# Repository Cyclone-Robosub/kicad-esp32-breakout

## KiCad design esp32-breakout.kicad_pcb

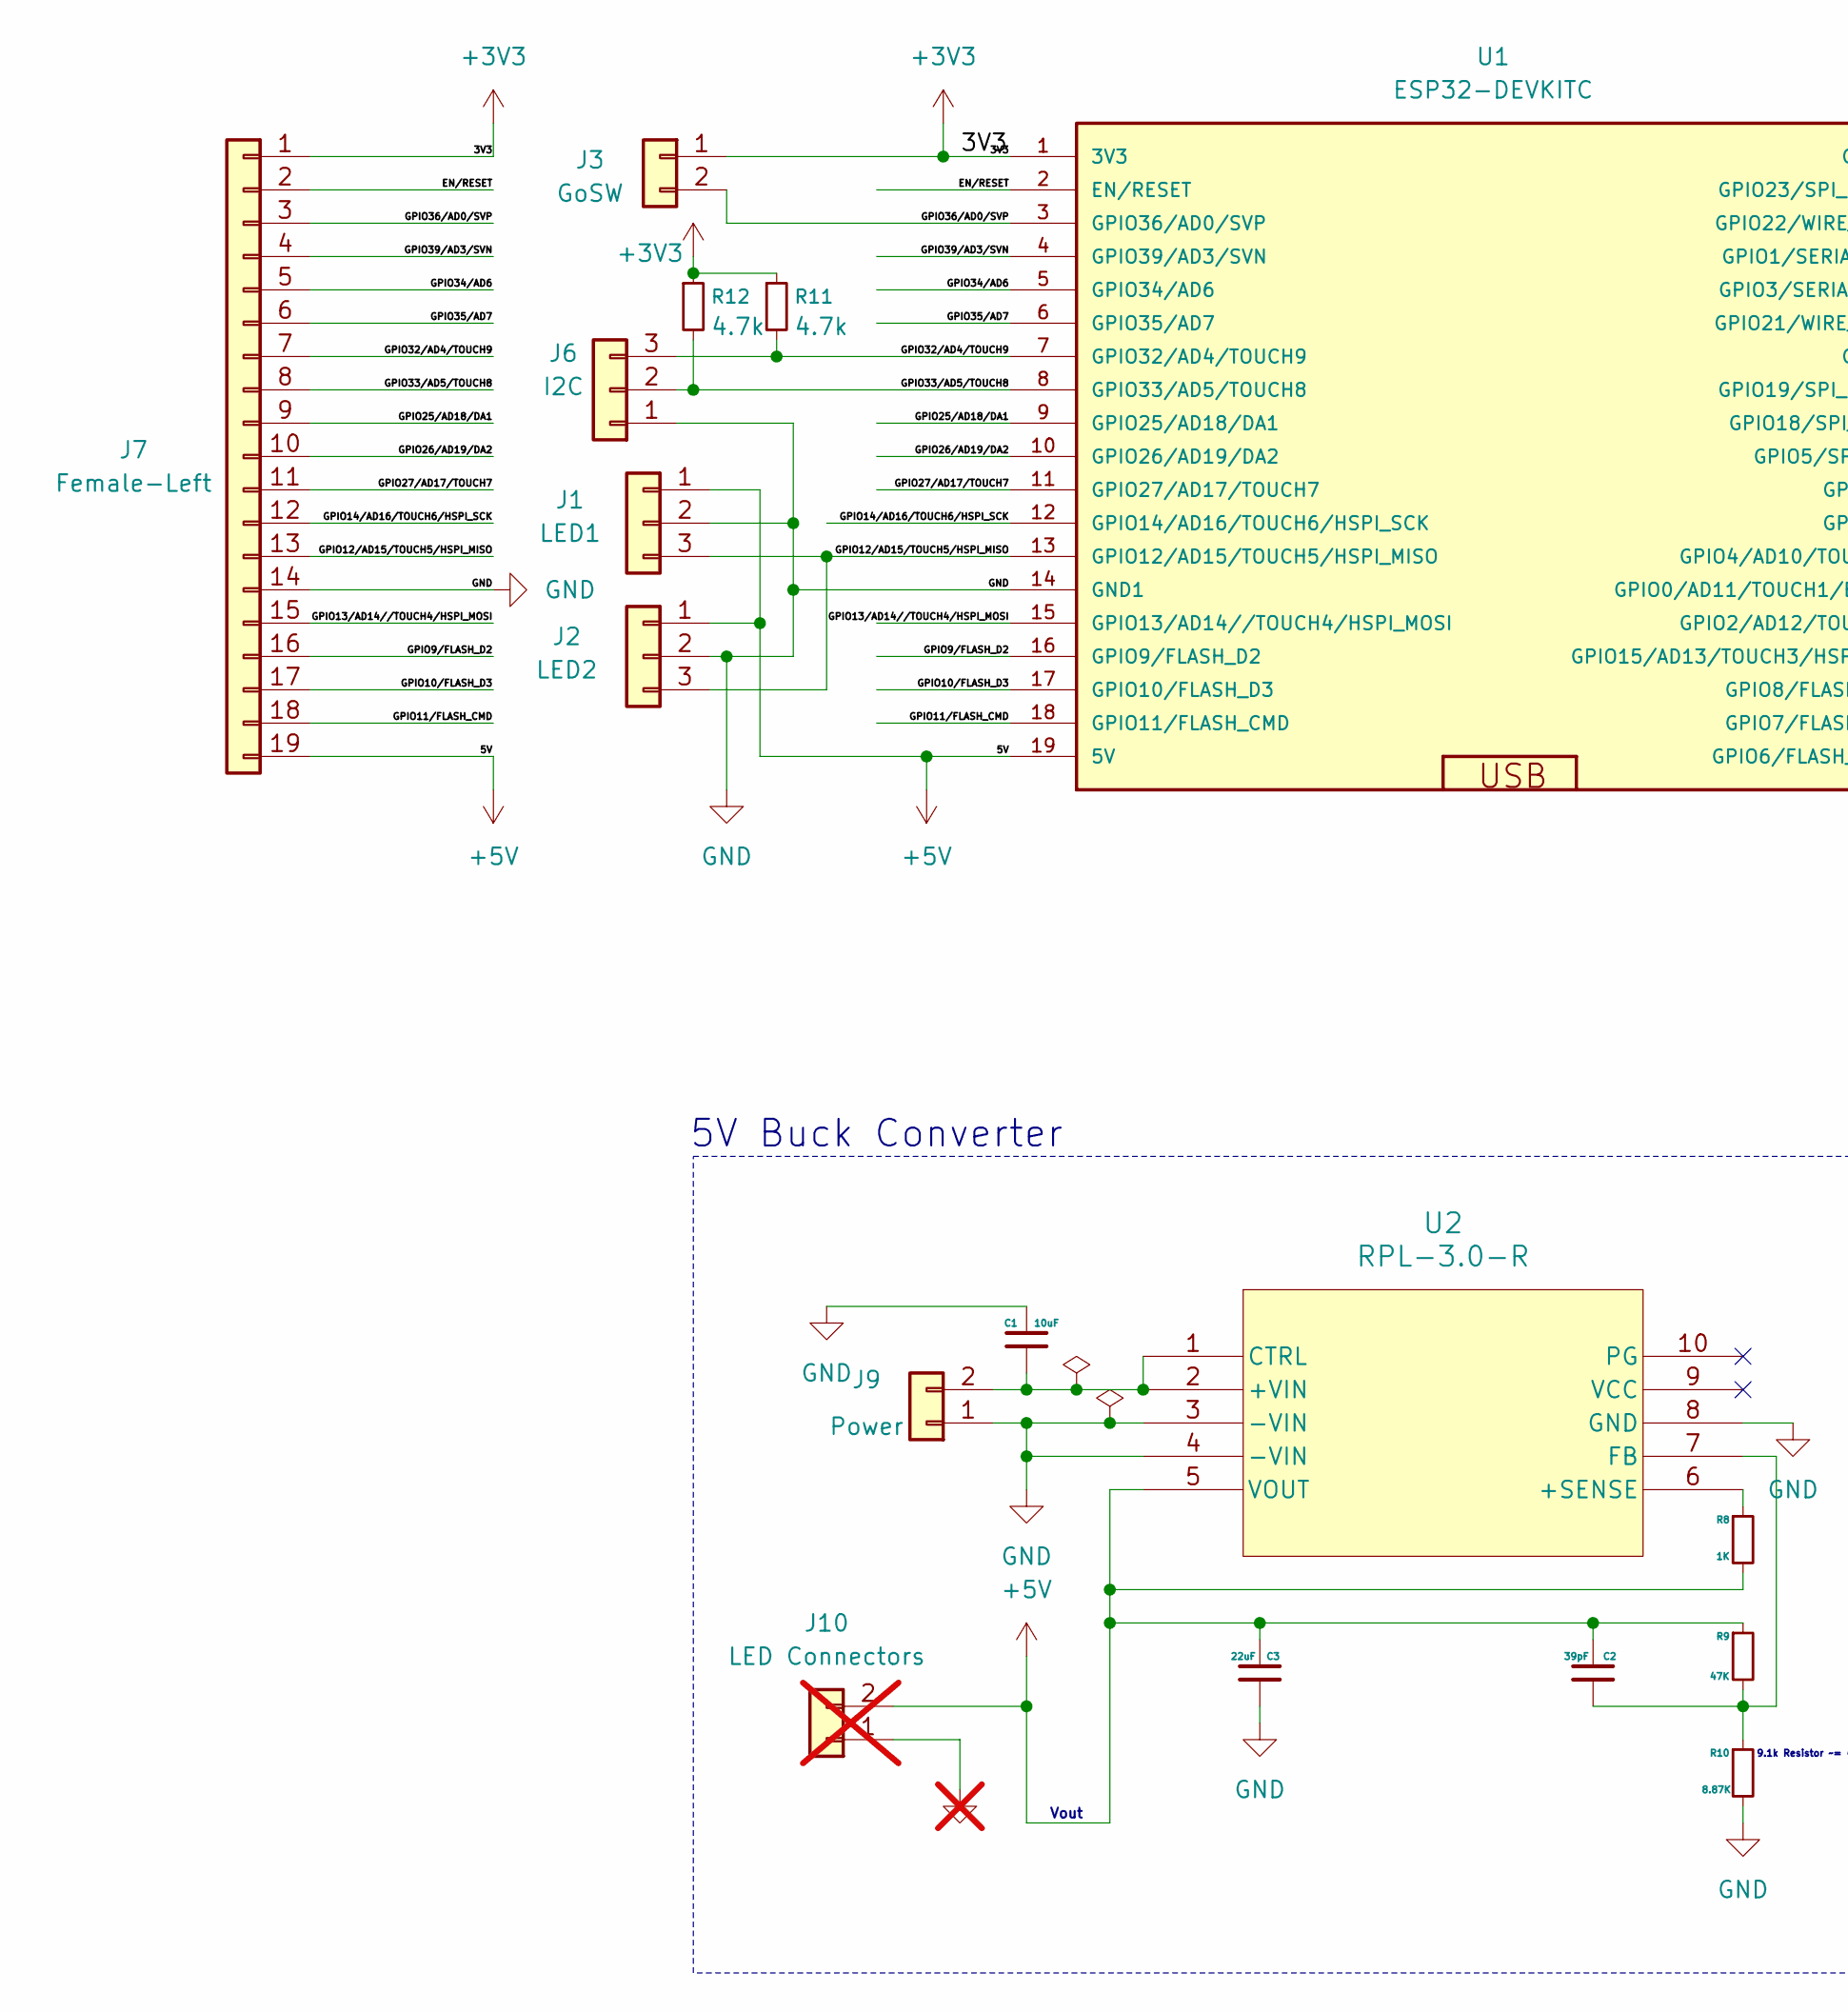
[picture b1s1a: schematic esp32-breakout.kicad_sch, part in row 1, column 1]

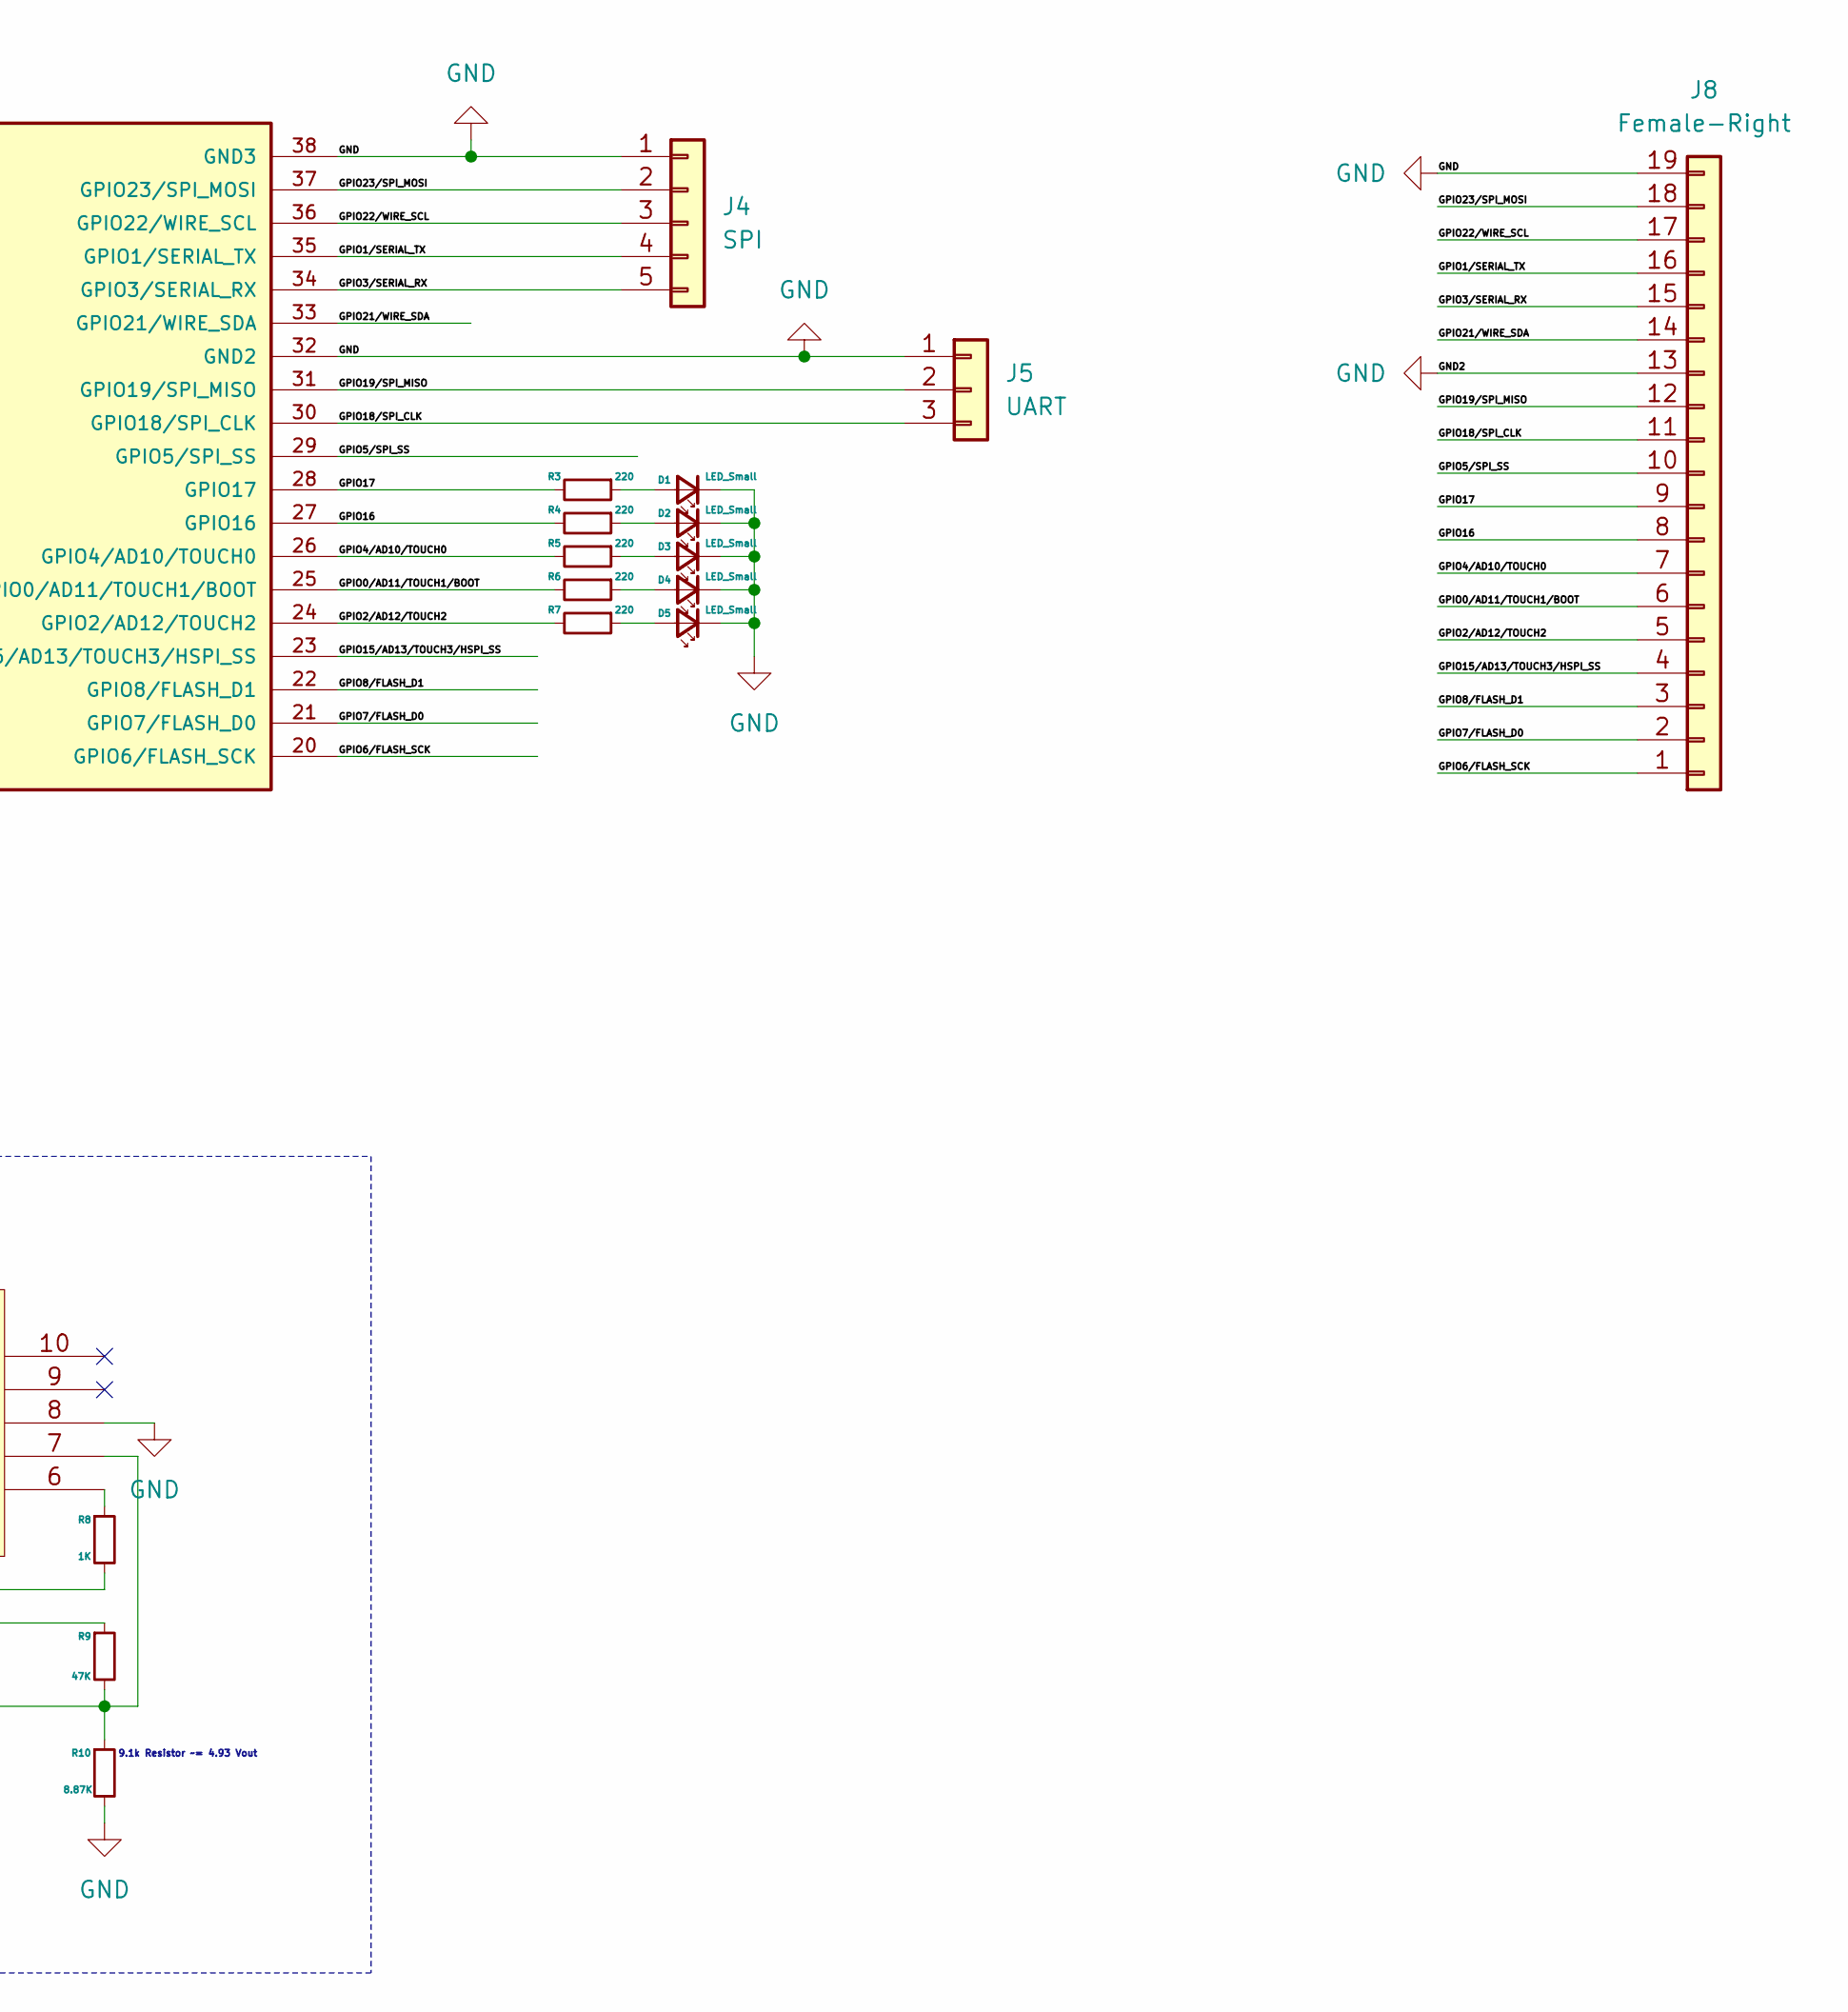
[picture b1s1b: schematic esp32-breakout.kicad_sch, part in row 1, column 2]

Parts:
C1: 10uF; C_0805_2012Metric_Pad1.18x1.45mm_HandSolder
C2: 39pF; C_0805_2012Metric_Pad1.18x1.45mm_HandSolder
C3: 22uF; C_0805_2012Metric_Pad1.18x1.45mm_HandSolder
D1, D2, D3, D4, D5: LED_Small; LED_0805_2012Metric_Pad1.15x1.40mm_HandSolder
J1: LED1; JST_PH_B3B-PH-K_1x03_P2.00mm_Vertical
J2: LED2; JST_PH_B3B-PH-K_1x03_P2.00mm_Vertical
J3: GoSW; JST_PH_B2B-PH-K_1x02_P2.00mm_Vertical
J4: SPI; JST_PH_B5B-PH-K_1x05_P2.00mm_Vertical
J5: UART; JST_PH_B3B-PH-K_1x03_P2.00mm_Vertical
J6: I2C; JST_PH_B3B-PH-K_1x03_P2.00mm_Vertical
J7: Female-Left; PinSocket_1x19_P2.54mm_Vertical
J8: Female-Right; PinSocket_1x19_P2.54mm_Vertical
J9: Power; JST_PH_B2B-PH-K_1x02_P2.00mm_Vertical
J10: LED Connectors; LED_D5.0mm_IRGrey; not fitted
R3, R4, R5, R6, R7: 220; R_0805_2012Metric_Pad1.20x1.40mm_HandSolder
R8: 1K; R_0805_2012Metric_Pad1.20x1.40mm_HandSolder
R9: 47K; R_0805_2012Metric_Pad1.20x1.40mm_HandSolder
R10: 8.87K; R_0805_2012Metric_Pad1.20x1.40mm_HandSolder
R11, R12: 4.7k; R_0805_2012Metric_Pad1.20x1.40mm_HandSolder
U1: ESP32-DEVKITC; MODULE_ESP32-DEVKITC
U2: RPL-3.0-R; LGA10_3X3X1.45_RCP

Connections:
+3V3: J3.1, J7.1, R11.1, R12.1, U1.1 (3V3)
+5V: C2.1, C3.1, J1.1, J2.1, J7.19, J10.2, R8.2, R9.1, U1.19 (5V), U2.5 (VOUT)
/EN/RESET: J7.2, U1.2 (EN/RESET)
/GPIO0/AD11/TOUCH1/BOOT: J8.6, R6.2, U1.25 (GPIO0/AD11/TOUCH1/BOOT)
/GPIO1/SERIAL_TX: J4.4, J8.16, U1.35 (GPIO1/SERIAL_TX)
/GPIO2/AD12/TOUCH2: J8.5, R7.2, U1.24 (GPIO2/AD12/TOUCH2)
/GPIO3/SERIAL_RX: J4.5, J8.15, U1.34 (GPIO3/SERIAL_RX)
/GPIO4/AD10/TOUCH0: J8.7, R5.2, U1.26 (GPIO4/AD10/TOUCH0)
/GPIO5/SPI_SS: J8.10, U1.29 (GPIO5/SPI_SS)
/GPIO6/FLASH_SCK: J8.1, U1.20 (GPIO6/FLASH_SCK)
/GPIO7/FLASH_D0: J8.2, U1.21 (GPIO7/FLASH_D0)
/GPIO8/FLASH_D1: J8.3, U1.22 (GPIO8/FLASH_D1)
/GPIO9/FLASH_D2: J7.16, U1.16 (GPIO9/FLASH_D2)
/GPIO10/FLASH_D3: J7.17, U1.17 (GPIO10/FLASH_D3)
/GPIO11/FLASH_CMD: J7.18, U1.18 (GPIO11/FLASH_CMD)
/GPIO12/AD15/TOUCH5/HSPI_MISO: J1.3, J2.3, J7.13, U1.13 (GPIO12/AD15/TOUCH5/HSPI_MISO)
/GPIO13/AD14//TOUCH4/HSPI_MOSI: J7.15, U1.15 (GPIO13/AD14//TOUCH4/HSPI_MOSI)
/GPIO14/AD16/TOUCH6/HSPI_SCK: J7.12, U1.12 (GPIO14/AD16/TOUCH6/HSPI_SCK)
/GPIO15/AD13/TOUCH3/HSPI_SS: J8.4, U1.23 (GPIO15/AD13/TOUCH3/HSPI_SS)
/GPIO16: J8.8, R4.2, U1.27 (GPIO16)
/GPIO17: J8.9, R3.2, U1.28 (GPIO17)
/GPIO18/SPI_CLK: J5.3, J8.11, U1.30 (GPIO18/SPI_CLK)
/GPIO19/SPI_MISO: J5.2, J8.12, U1.31 (GPIO19/SPI_MISO)
/GPIO21/WIRE_SDA: J8.14, U1.33 (GPIO21/WIRE_SDA)
/GPIO22/WIRE_SCL: J4.3, J8.17, U1.36 (GPIO22/WIRE_SCL)
/GPIO23/SPI_MOSI: J4.2, J8.18, U1.37 (GPIO23/SPI_MOSI)
/GPIO25/AD18/DA1: J7.9, U1.9 (GPIO25/AD18/DA1)
/GPIO26/AD19/DA2: J7.10, U1.10 (GPIO26/AD19/DA2)
/GPIO27/AD17/TOUCH7: J7.11, U1.11 (GPIO27/AD17/TOUCH7)
/GPIO32/AD4/TOUCH9: J6.3, J7.7, R11.2, U1.7 (GPIO32/AD4/TOUCH9)
/GPIO33/AD5/TOUCH8: J6.2, J7.8, R12.2, U1.8 (GPIO33/AD5/TOUCH8)
/GPIO34/AD6: J7.5, U1.5 (GPIO34/AD6)
/GPIO35/AD7: J7.6, U1.6 (GPIO35/AD7)
/GPIO36/AD0/SVP: J3.2, J7.3, U1.3 (GPIO36/AD0/SVP)
/GPIO39/AD3/SVN: J7.4, U1.4 (GPIO39/AD3/SVN)
GND: C1.1, C3.2, D1.1 (K), D2.1 (K), D3.1 (K), D4.1 (K), D5.1 (K), J1.2, J2.2, J4.1, J5.1, J6.1, J7.14, J8.13, J8.19, J9.1, J10.1, R10.2, U1.14 (GND1), U1.32 (GND2), U1.38 (GND3), U2.3 (-VIN), U2.4 (-VIN), U2.8 (GND)
unnamed: D1.2 (A), R3.1
unnamed: D2.2 (A), R4.1
unnamed: D3.2 (A), R5.1
unnamed: D4.2 (A), R6.1
unnamed: D5.2 (A), R7.1
unnamed: C1.2, J9.2, U2.1 (CTRL), U2.2 (+VIN)
unnamed: R8.1, U2.6 (+SENSE)
unnamed: C2.2, R9.2, R10.1, U2.7 (FB)

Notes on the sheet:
9.1k Resistor ~= 4.93 Vout
Vout
5V Buck Converter

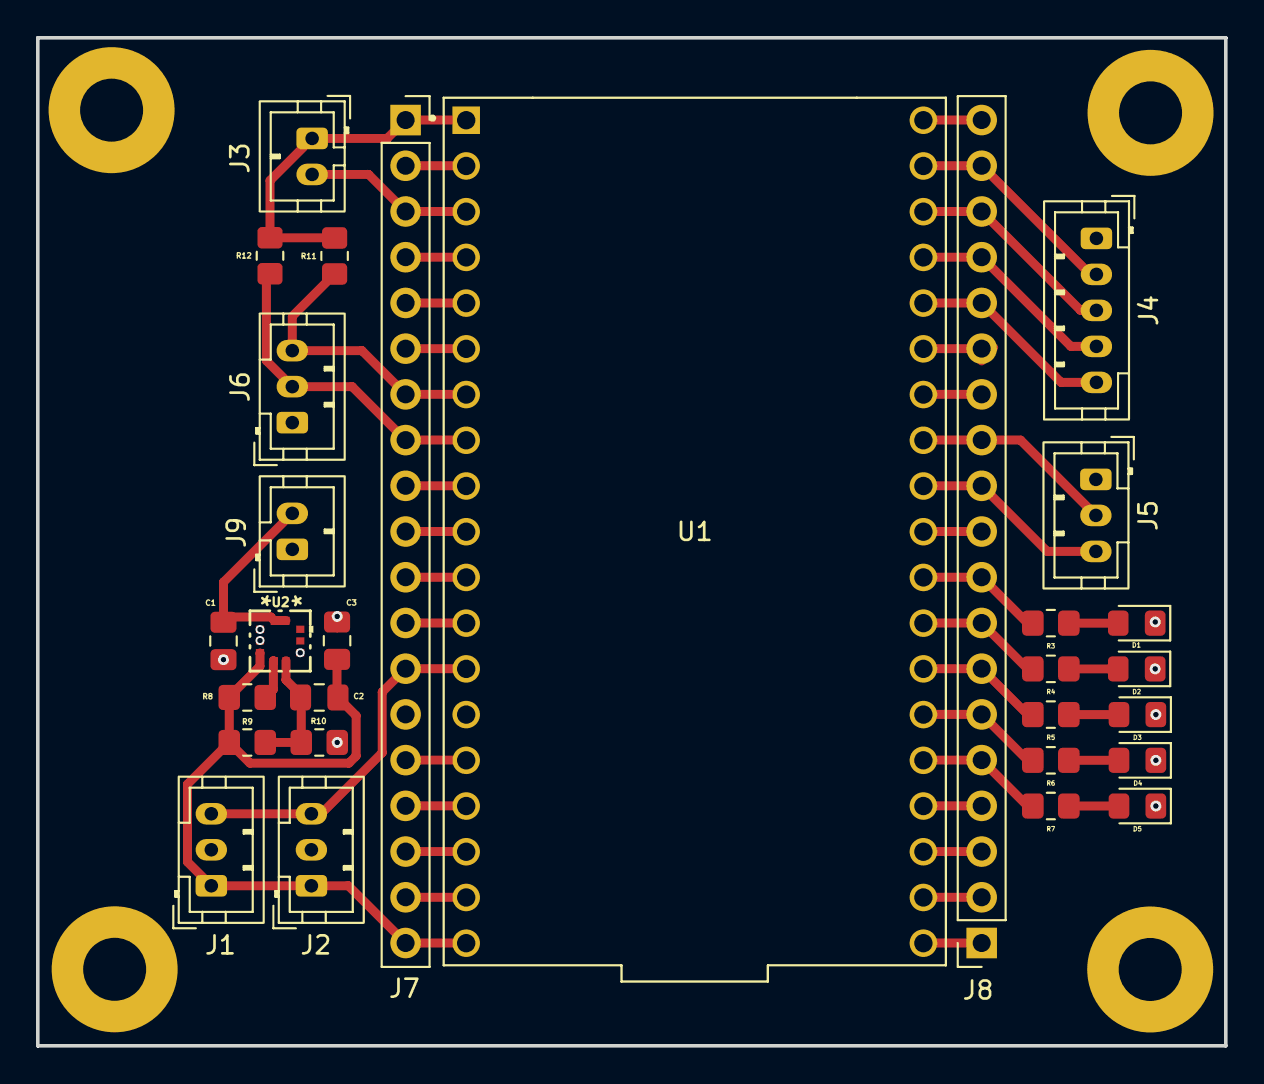
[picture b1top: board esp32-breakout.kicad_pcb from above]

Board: 2 copper layers, 66.0 x 56.0 mm, 29 parts (0 on the bottom side), 44 nets.
